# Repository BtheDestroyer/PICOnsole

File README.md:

# PICOnsole

Simple OS made from scratch for the Raspberry Pi Pico with the intention of being used to launch games.

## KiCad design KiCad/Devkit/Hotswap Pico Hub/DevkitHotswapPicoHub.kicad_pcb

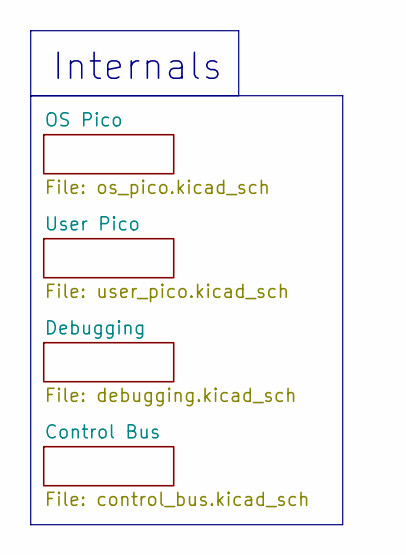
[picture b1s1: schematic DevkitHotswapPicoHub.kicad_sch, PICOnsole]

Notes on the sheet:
Internals

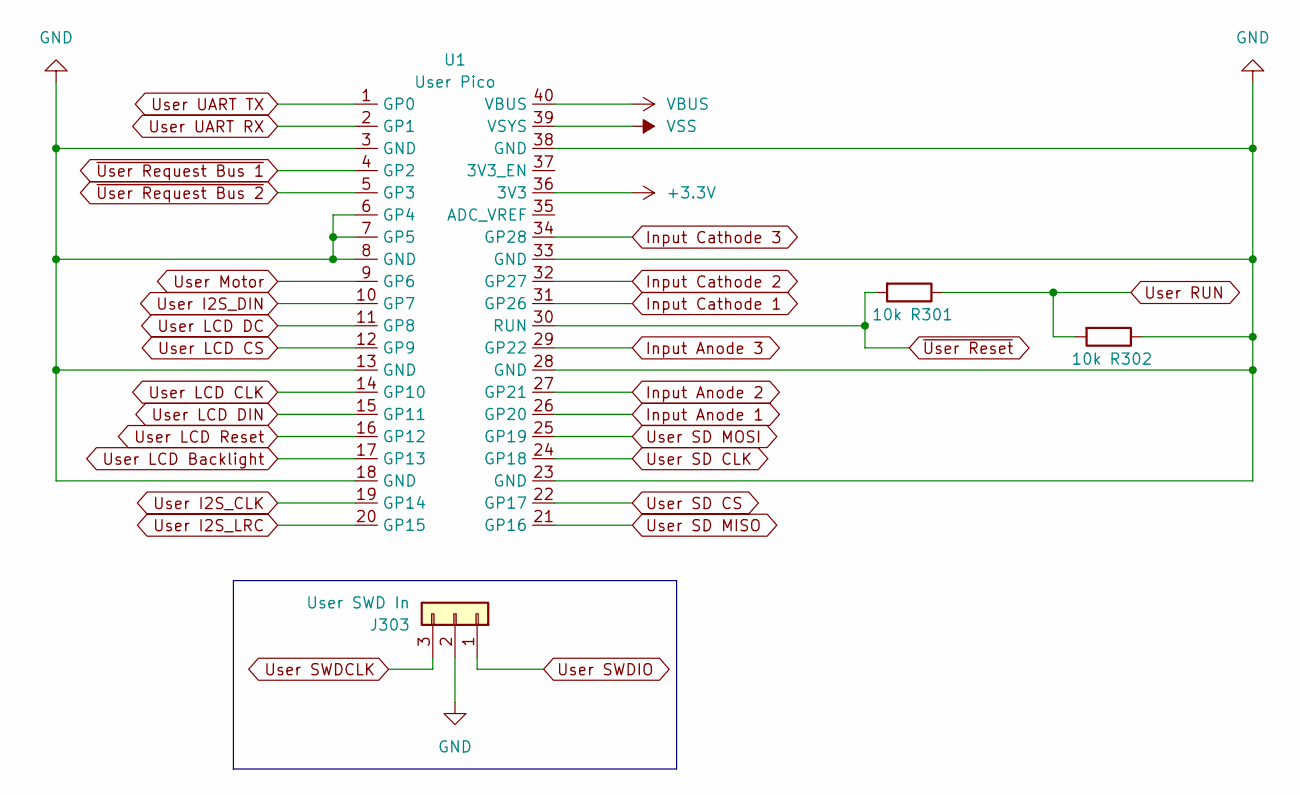
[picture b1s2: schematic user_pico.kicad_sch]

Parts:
J303: User SWD In; PinHeader_1x03_P2.54mm_Vertical
R301, R302: 10k; R_0805_2012Metric
U1: User Pico; Raspberry_Pi_Pico

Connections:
GND: J303.2, R302.1; also elsewhere on the board
User RUN: R301.1, R302.2; also elsewhere on the board
User SWDCLK: J303.3; also elsewhere on the board
User SWDIO: J303.1; also elsewhere on the board
~User Reset: R301.2; also elsewhere on the board

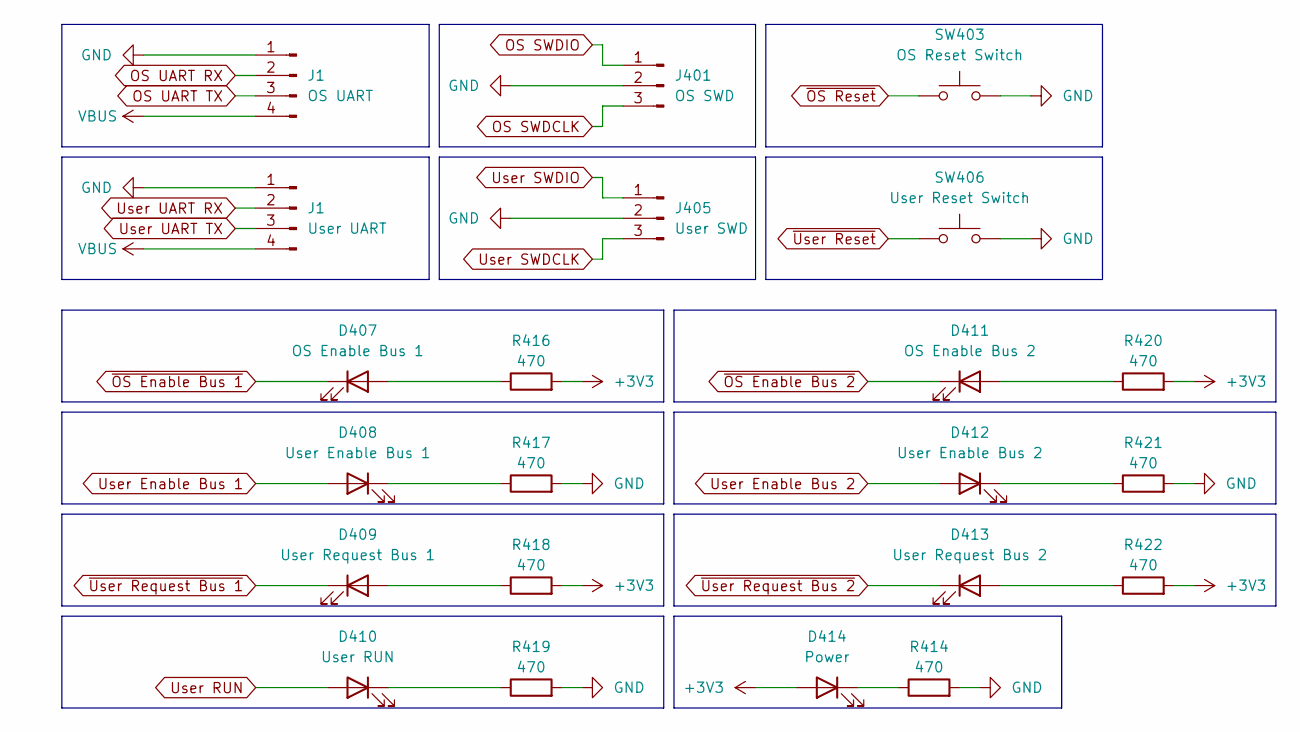
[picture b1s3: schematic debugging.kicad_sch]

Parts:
D407: OS Enable Bus 1; LED_D5.0mm
D408: User Enable Bus 1; LED_D5.0mm
D409: User Request Bus 1; LED_D5.0mm
D410: User RUN; LED_D5.0mm
D411: OS Enable Bus 2; LED_D5.0mm
D412: User Enable Bus 2; LED_D5.0mm
D413: User Request Bus 2; LED_D5.0mm
D414: Power; LED_D5.0mm
J1: OS UART; PinHeader_1x04_P2.54mm_Vertical
J401: OS SWD; PinSocket_1x03_P2.54mm_Vertical
J405: User SWD; PinSocket_1x03_P2.54mm_Vertical
R414, R416, R417, R418, R419, R420, R421, R422: 470; R_0805_2012Metric
SW403: OS Reset Switch; SW_PUSH-12mm
SW406: User Reset Switch; SW_PUSH-12mm

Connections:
GND: J401.2, J405.2, R414.2, R417.2, R419.2, R421.2, SW403.1, SW406.2; also elsewhere on the board
unnamed: D407.2 (A), R416.1
unnamed: D408.1 (K), R417.1
unnamed: D409.2 (A), R418.1
unnamed: D410.1 (K), R419.1
unnamed: D411.2 (A), R420.1
unnamed: D412.1 (K), R421.1
unnamed: D413.2 (A), R422.1
unnamed: D414.1 (K), R414.1
OS SWDCLK: J401.3; also elsewhere on the board
OS SWDIO: J401.1; also elsewhere on the board
User Enable Bus 1: D407.1 (K), D408.2 (A); also elsewhere on the board
User Enable Bus 2: D411.1 (K), D412.2 (A); also elsewhere on the board
User RUN: D410.2 (A); also elsewhere on the board
User SWDCLK: J405.3; also elsewhere on the board
User SWDIO: J405.1; also elsewhere on the board
~OS Reset: SW403.2; also elsewhere on the board
~User Request Bus 1: D409.1 (K); also elsewhere on the board
~User Request Bus 2: D413.1 (K); also elsewhere on the board
~User Reset: SW406.1; also elsewhere on the board

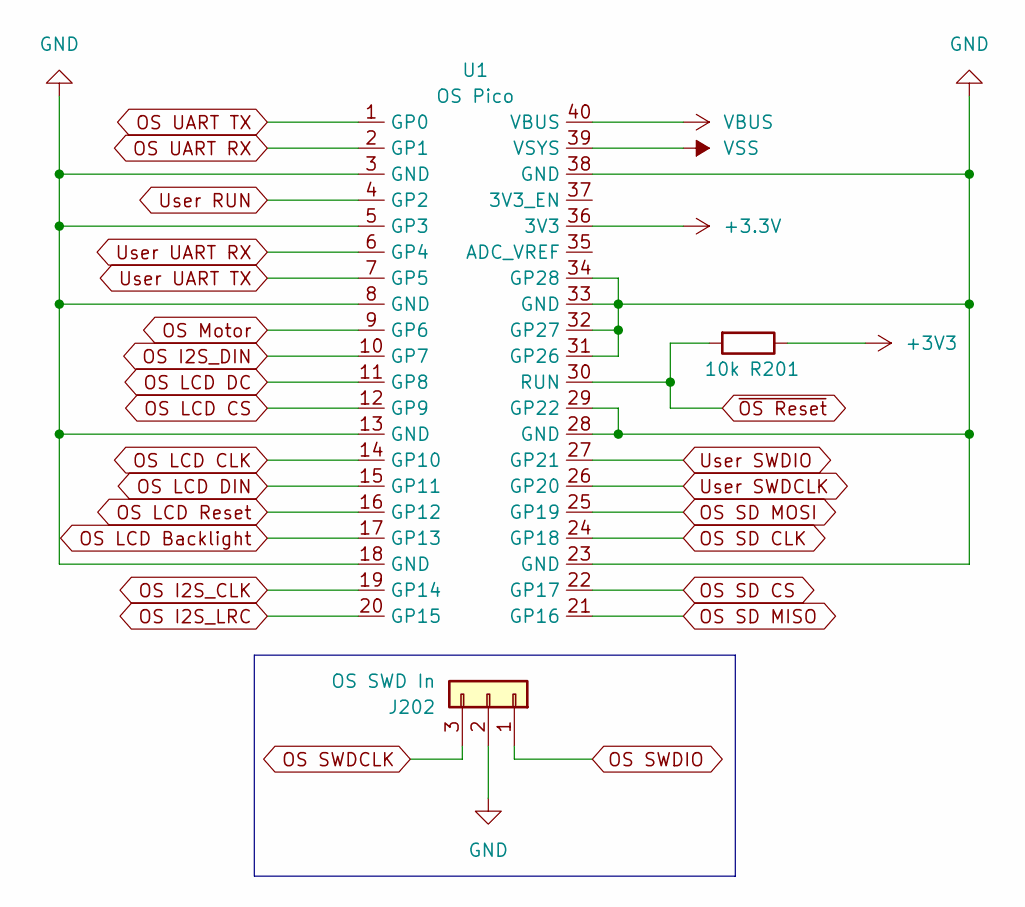
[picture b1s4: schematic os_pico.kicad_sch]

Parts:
J202: OS SWD In; PinHeader_1x03_P2.54mm_Vertical
R201: 10k; R_0805_2012Metric
U1: OS Pico; Raspberry_Pi_Pico

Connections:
GND: J202.2; also elsewhere on the board
OS SWDCLK: J202.3; also elsewhere on the board
OS SWDIO: J202.1; also elsewhere on the board
~OS Reset: R201.2; also elsewhere on the board

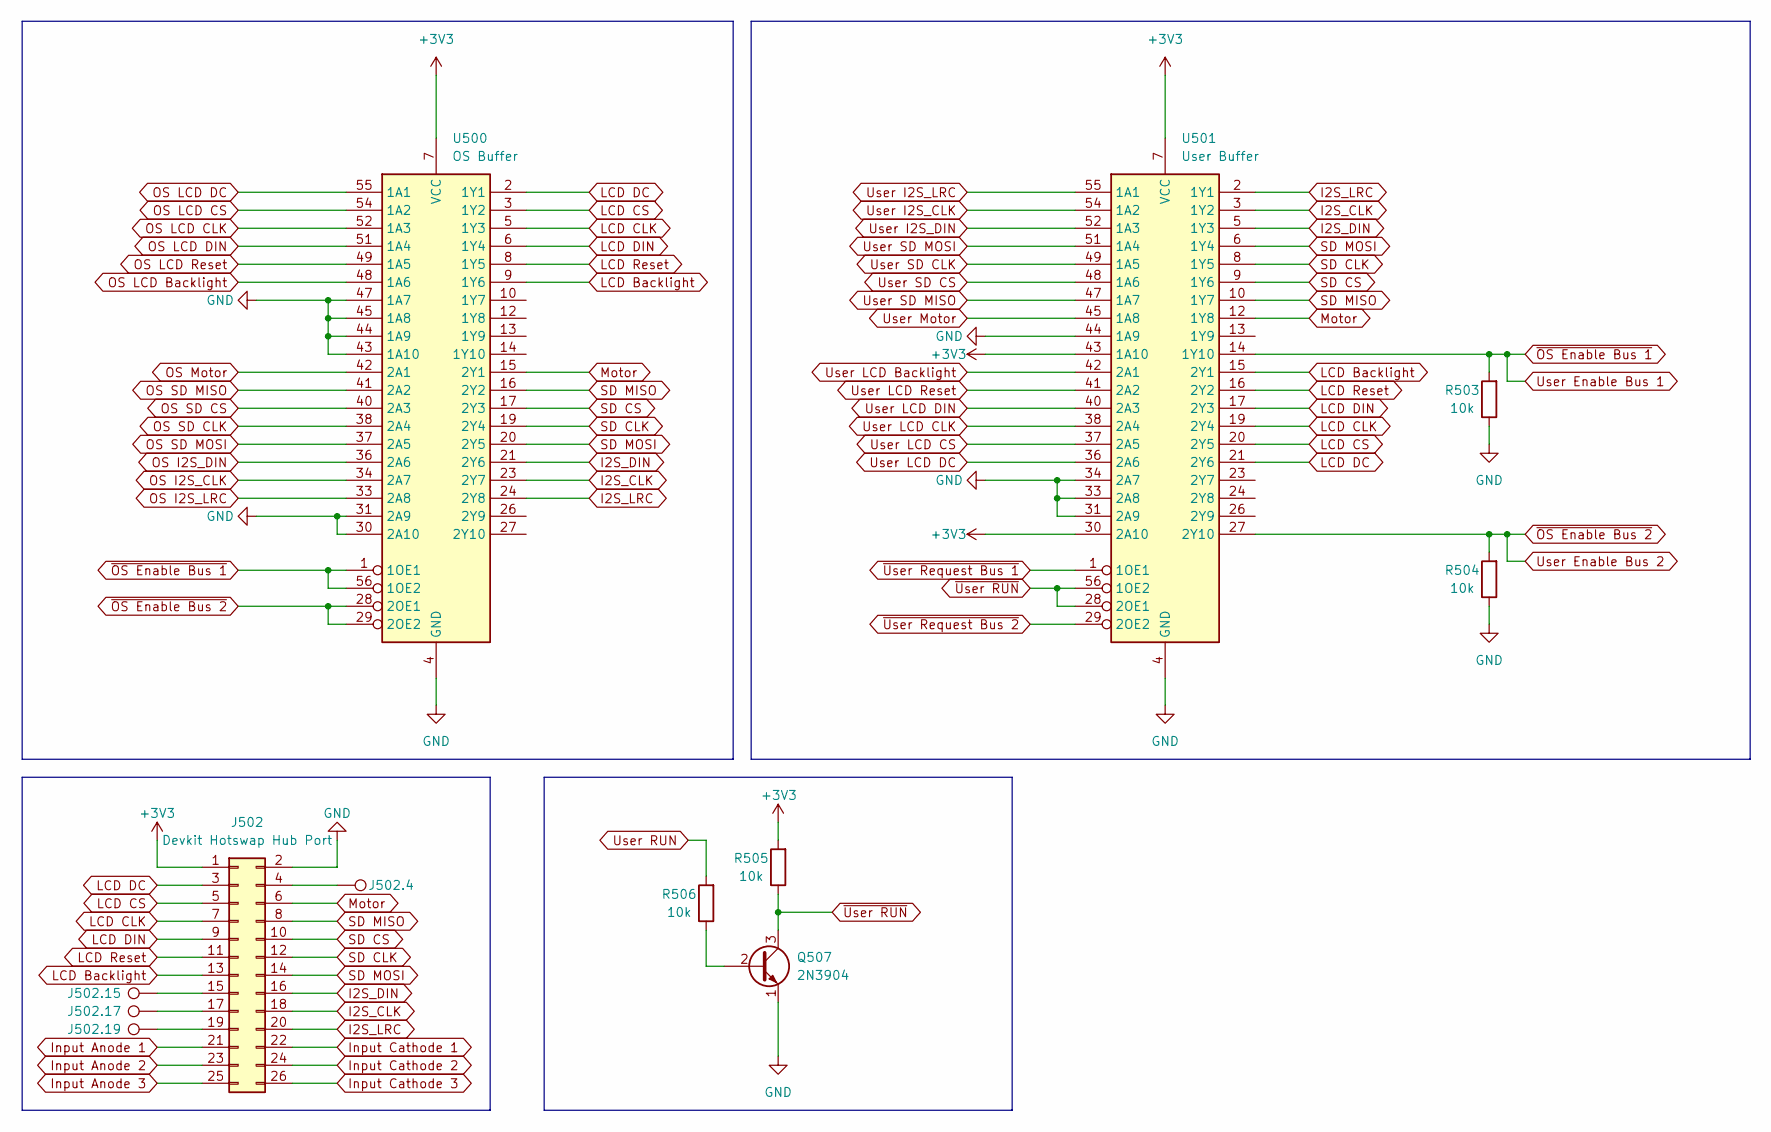
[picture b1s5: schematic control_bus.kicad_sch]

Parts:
J502: Devkit Hotswap Hub Port; PinHeader_2x13_P2.54mm_Vertical
J502.4, J502.15, J502.17, J502.19: TestPoint; TestPoint_Pad_1.5x1.5mm
Q507: 2N3904; TO-92_Inline
R503, R504, R505, R506: 10k; R_0805_2012Metric
U500: OS Buffer; TSSOP-56_6.1x14mm_P0.5mm
U501: User Buffer; TSSOP-56_6.1x14mm_P0.5mm

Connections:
GND: J502.2, Q507.1 (E), R503.1, R504.1, U500.4 (GND), U500.11 (GND), U500.18 (GND), U500.25 (GND), U500.30 (2A10), U500.31 (2A9), U500.32 (GND), U500.39 (GND), U500.43 (1A10), U500.44 (1A9), U500.45 (1A8), U500.46 (GND), U500.47 (1A7), U500.53 (GND), U501.4 (GND), U501.11 (GND), U501.18 (GND), U501.25 (GND), U501.31 (2A9), U501.32 (GND), U501.33 (2A8), U501.34 (2A7), U501.39 (GND), U501.44 (1A9), U501.46 (GND), U501.53 (GND); also elsewhere on the board
I2S_CLK: J502.18, U500.23 (2Y7), U501.3 (1Y2)
I2S_DIN: J502.16, U500.21 (2Y6), U501.5 (1Y3)
I2S_LRC: J502.20, U500.24 (2Y8), U501.2 (1Y1)
Input Anode 1: J502.21; also elsewhere on the board
Input Anode 2: J502.23; also elsewhere on the board
Input Anode 3: J502.25; also elsewhere on the board
Input Cathode 1: J502.22; also elsewhere on the board
Input Cathode 2: J502.24; also elsewhere on the board
Input Cathode 3: J502.26; also elsewhere on the board
LCD Backlight: J502.13, U500.9 (1Y6), U501.15 (2Y1)
LCD CLK: J502.7, U500.5 (1Y3), U501.19 (2Y4)
LCD CS: J502.5, U500.3 (1Y2), U501.20 (2Y5)
LCD DC: J502.3, U500.2 (1Y1), U501.21 (2Y6)
LCD DIN: J502.9, U500.6 (1Y4), U501.17 (2Y3)
LCD Reset: J502.11, U500.8 (1Y5), U501.16 (2Y2)
Motor: J502.6, U500.15 (2Y1), U501.12 (1Y8)
unnamed: J502.4, J502.4.1
unnamed: J502.15, J502.15.1
unnamed: J502.17, J502.17.1
unnamed: J502.19, J502.19.1
unnamed: Q507.2 (B), R506.1
OS I2S_CLK: U500.34 (2A7); also elsewhere on the board
OS I2S_DIN: U500.36 (2A6); also elsewhere on the board
OS I2S_LRC: U500.33 (2A8); also elsewhere on the board
OS LCD Backlight: U500.48 (1A6); also elsewhere on the board
OS LCD CLK: U500.52 (1A3); also elsewhere on the board
OS LCD CS: U500.54 (1A2); also elsewhere on the board
OS LCD DC: U500.55 (1A1); also elsewhere on the board
OS LCD DIN: U500.51 (1A4); also elsewhere on the board
OS LCD Reset: U500.49 (1A5); also elsewhere on the board
OS Motor: U500.42 (2A1); also elsewhere on the board
OS SD CLK: U500.38 (2A4); also elsewhere on the board
OS SD CS: U500.40 (2A3); also elsewhere on the board
OS SD MISO: U500.41 (2A2); also elsewhere on the board
OS SD MOSI: U500.37 (2A5); also elsewhere on the board
SD CLK: J502.12, U500.19 (2Y4), U501.8 (1Y5)
SD CS: J502.10, U500.17 (2Y3), U501.9 (1Y6)
SD MISO: J502.8, U500.16 (2Y2), U501.10 (1Y7)
SD MOSI: J502.14, U500.20 (2Y5), U501.6 (1Y4)
User Enable Bus 1: R503.2, U500.1 (1OE1), U500.56 (1OE2), U501.14 (1Y10); also elsewhere on the board
User Enable Bus 2: R504.2, U500.28 (2OE1), U500.29 (2OE2), U501.27 (2Y10); also elsewhere on the board
User I2S_CLK: U501.54 (1A2); also elsewhere on the board
User I2S_DIN: U501.52 (1A3); also elsewhere on the board
User I2S_LRC: U501.55 (1A1); also elsewhere on the board
User LCD Backlight: U501.42 (2A1); also elsewhere on the board
User LCD CLK: U501.38 (2A4); also elsewhere on the board
User LCD CS: U501.37 (2A5); also elsewhere on the board
User LCD DC: U501.36 (2A6); also elsewhere on the board
User LCD DIN: U501.40 (2A3); also elsewhere on the board
User LCD Reset: U501.41 (2A2); also elsewhere on the board
User Motor: U501.45 (1A8); also elsewhere on the board
User RUN: R506.2; also elsewhere on the board
User SD CLK: U501.49 (1A5); also elsewhere on the board
User SD CS: U501.48 (1A6); also elsewhere on the board
User SD MISO: U501.47 (1A7); also elsewhere on the board
User SD MOSI: U501.51 (1A4); also elsewhere on the board
~User RUN: Q507.3 (C), R505.1, U501.28 (2OE1), U501.56 (1OE2)
~User Request Bus 1: U501.1 (1OE1); also elsewhere on the board
~User Request Bus 2: U501.29 (2OE2); also elsewhere on the board

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
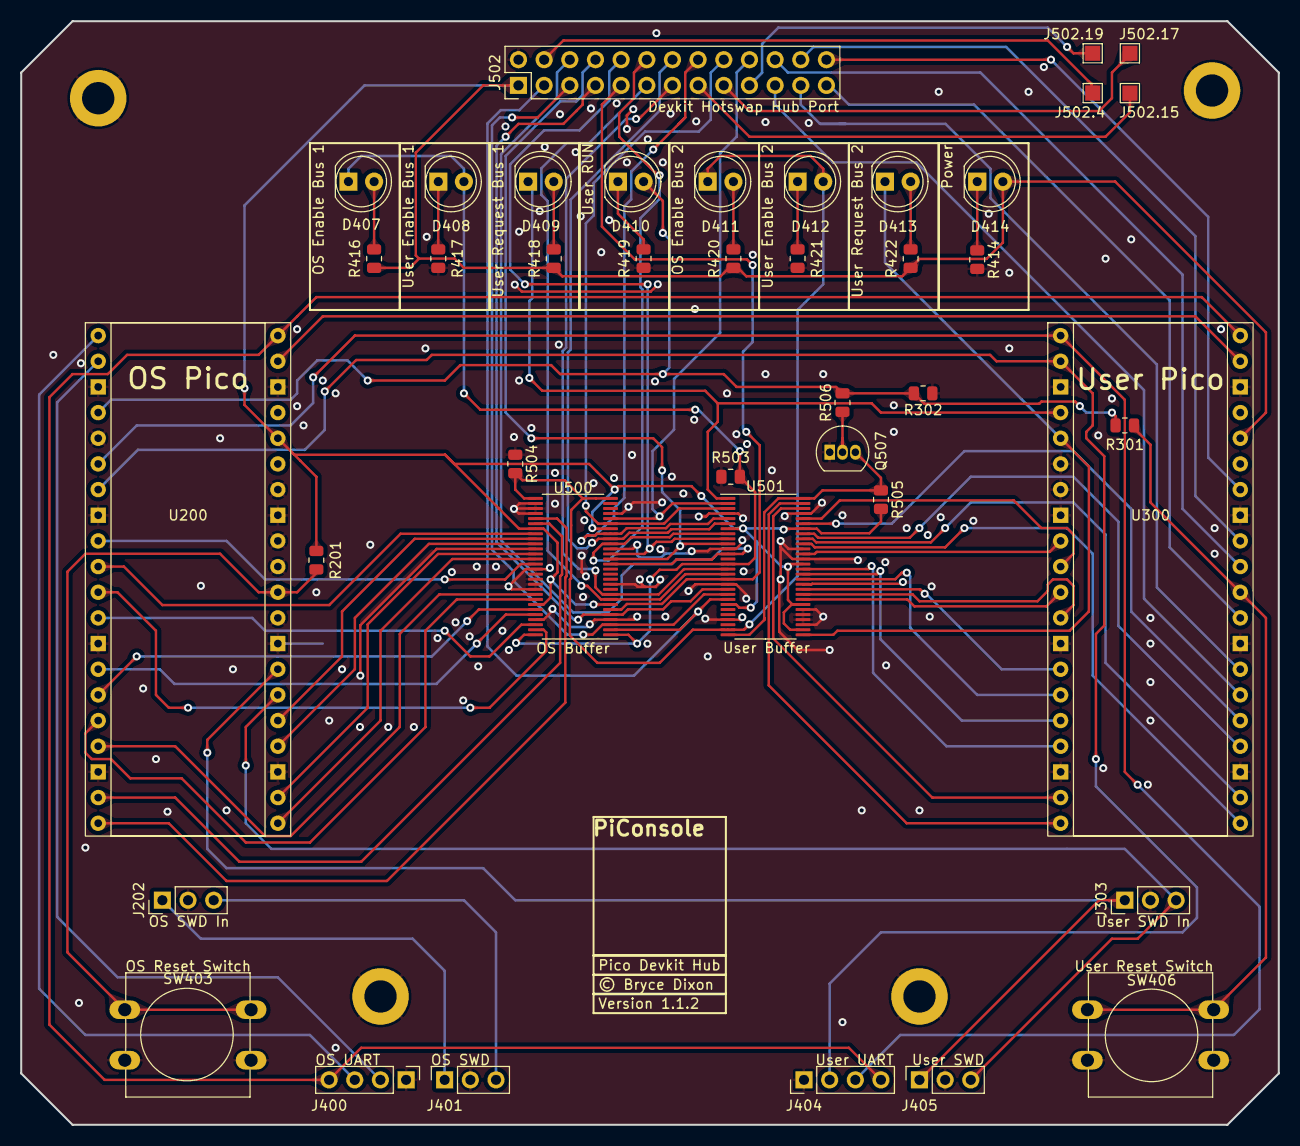
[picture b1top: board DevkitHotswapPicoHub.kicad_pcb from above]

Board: 2 copper layers, 124.5 x 109.2 mm, 41 parts (0 on the bottom side), 81 nets.

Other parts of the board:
J400: OS UART; PinHeader_1x04_P2.54mm_Vertical
J404: User UART; PinHeader_1x04_P2.54mm_Vertical
U200: OS Pico; Raspberry_Pi_Pico
U300: User Pico; Raspberry_Pi_Pico

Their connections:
GND: J400.1, J404.1, U200.3 (GND), U200.5 (GP3), U200.8 (GND), U200.13 (GND), U200.18 (GND), U200.23 (GND), U200.28 (GND), U200.29 (GP22), U200.31 (GP26), U200.32 (GP27), U200.33 (GND), U200.34 (GP28), U200.38 (GND), U300.3 (GND), U300.6 (GP4), U300.7 (GP5), U300.8 (GND), U300.13 (GND), U300.18 (GND), U300.23 (GND), U300.28 (GND), U300.33 (GND), U300.38 (GND); also elsewhere on the board
Input Anode 1: U300.26 (GP20); also elsewhere on the board
Input Anode 2: U300.27 (GP21); also elsewhere on the board
Input Anode 3: U300.29 (GP22); also elsewhere on the board
Input Cathode 1: U300.31 (GP26); also elsewhere on the board
Input Cathode 2: U300.32 (GP27); also elsewhere on the board
Input Cathode 3: U300.34 (GP28); also elsewhere on the board
OS I2S_CLK: U200.19 (GP14); also elsewhere on the board
OS I2S_DIN: U200.10 (GP7); also elsewhere on the board
OS I2S_LRC: U200.20 (GP15); also elsewhere on the board
OS LCD Backlight: U200.17 (GP13); also elsewhere on the board
OS LCD CLK: U200.14 (GP10); also elsewhere on the board
OS LCD CS: U200.12 (GP9); also elsewhere on the board
OS LCD DC: U200.11 (GP8); also elsewhere on the board
OS LCD DIN: U200.15 (GP11); also elsewhere on the board
OS LCD Reset: U200.16 (GP12); also elsewhere on the board
OS Motor: U200.9 (GP6); also elsewhere on the board
OS SD CLK: U200.24 (GP18); also elsewhere on the board
OS SD CS: U200.22 (GP17); also elsewhere on the board
OS SD MISO: U200.21 (GP16); also elsewhere on the board
OS SD MOSI: U200.25 (GP19); also elsewhere on the board
OS UART RX: J400.2, U200.2 (GP1)
OS UART TX: J400.3, U200.1 (GP0)
User I2S_CLK: U300.19 (GP14); also elsewhere on the board
User I2S_DIN: U300.10 (GP7); also elsewhere on the board
User I2S_LRC: U300.20 (GP15); also elsewhere on the board
User LCD Backlight: U300.17 (GP13); also elsewhere on the board
User LCD CLK: U300.14 (GP10); also elsewhere on the board
User LCD CS: U300.12 (GP9); also elsewhere on the board
User LCD DC: U300.11 (GP8); also elsewhere on the board
User LCD DIN: U300.15 (GP11); also elsewhere on the board
User LCD Reset: U300.16 (GP12); also elsewhere on the board
User Motor: U300.9 (GP6); also elsewhere on the board
User RUN: U200.4 (GP2); also elsewhere on the board
User SD CLK: U300.24 (GP18); also elsewhere on the board
User SD CS: U300.22 (GP17); also elsewhere on the board
User SD MISO: U300.21 (GP16); also elsewhere on the board
User SD MOSI: U300.25 (GP19); also elsewhere on the board
User SWDCLK: U200.26 (GP20); also elsewhere on the board
User SWDIO: U200.27 (GP21); also elsewhere on the board
User UART RX: J404.2, U200.6 (GP4), U300.2 (GP1)
User UART TX: J404.3, U200.7 (GP5), U300.1 (GP0)
VBUS: J400.4, J404.4, U200.40 (VBUS), U300.40 (VBUS)
VSS: U200.39 (VSYS), U300.39 (VSYS)
~OS Reset: U200.30 (RUN); also elsewhere on the board
~User Request Bus 1: U300.4 (GP2); also elsewhere on the board
~User Request Bus 2: U300.5 (GP3); also elsewhere on the board
~User Reset: U300.30 (RUN); also elsewhere on the board

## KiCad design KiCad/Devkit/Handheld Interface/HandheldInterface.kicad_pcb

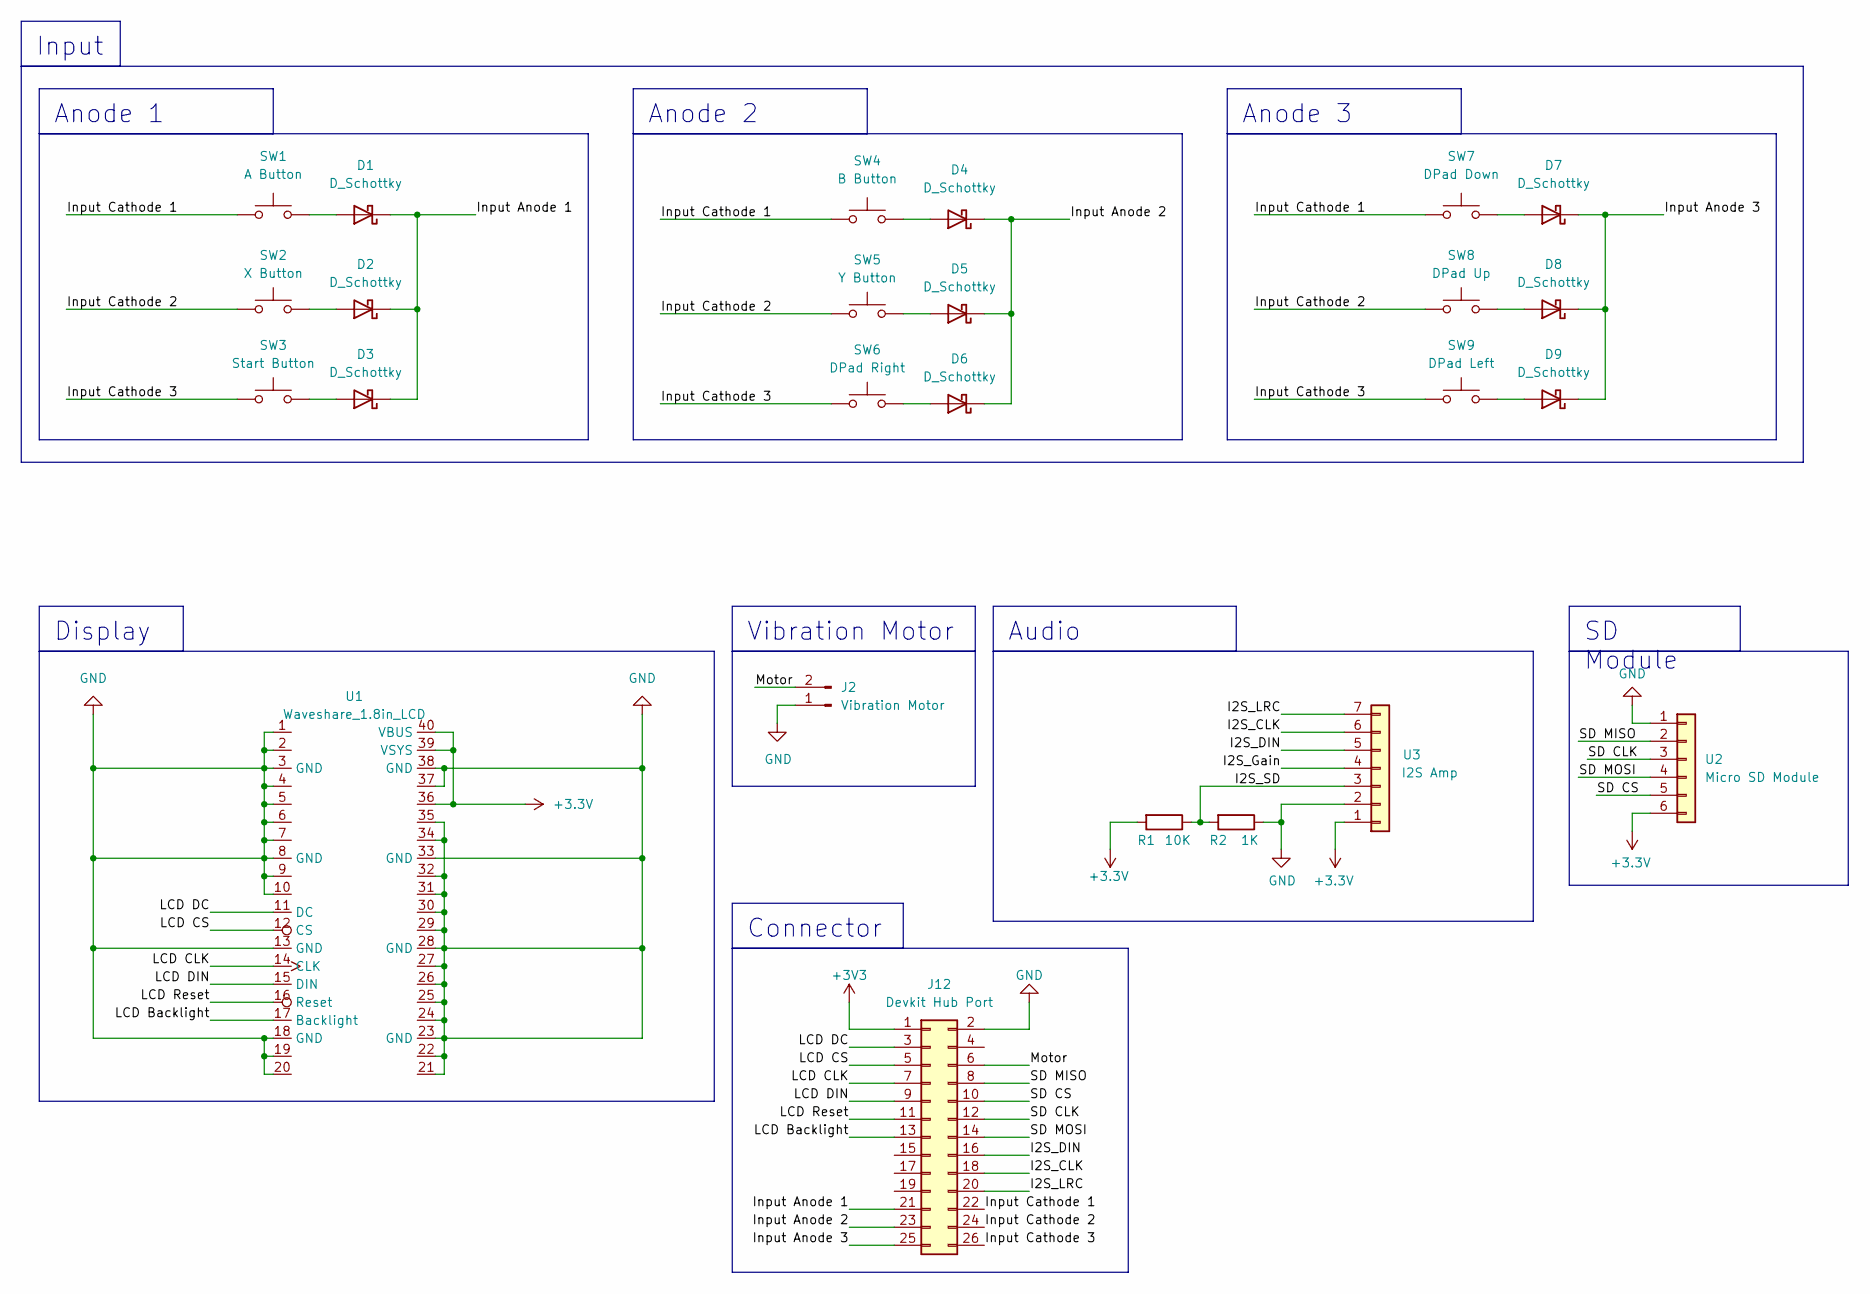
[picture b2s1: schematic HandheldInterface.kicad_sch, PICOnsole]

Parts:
D1, D2, D3, D4, D5, D6, D7, D8, D9: D_Schottky; D_A-405_P10.16mm_Horizontal
J2: Vibration Motor; PinHeader_1x02_P2.54mm_Vertical
J12: Devkit Hub Port; PinHeader_2x13_P2.54mm_Vertical
R1: 10K; R_0805_2012Metric_Pad1.20x1.40mm_HandSolder
R2: 1K; R_0805_2012Metric_Pad1.20x1.40mm_HandSolder
SW1: A Button; SW_PUSH-12mm
SW2: X Button; SW_PUSH-12mm
SW3: Start Button; SW_PUSH_6mm
SW4: B Button; SW_PUSH-12mm
SW5: Y Button; SW_PUSH-12mm
SW6: DPad Right; SW_PUSH-12mm
SW7: DPad Down; SW_PUSH-12mm
SW8: DPad Up; SW_PUSH-12mm
SW9: DPad Left; SW_PUSH-12mm
U1: Waveshare_1.8in_LCD
U2: Micro SD Module; PinHeader_1x06_P2.54mm_Vertical
U3: I2S Amp; PinHeader_1x07_P2.54mm_Vertical

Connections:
/I2S_CLK: U3.6; also elsewhere on the board
/I2S_DIN: U3.5; also elsewhere on the board
/I2S_Gain: U3.4
/I2S_LRC: U3.7; also elsewhere on the board
/I2S_SD: R1.1, R2.2, U3.3
/Input Anode 1: D1.1 (K), D2.1 (K), D3.1 (K); also elsewhere on the board
/Input Anode 2: D4.1 (K), D5.1 (K), D6.1 (K); also elsewhere on the board
/Input Anode 3: D7.1 (K), D8.1 (K), D9.1 (K); also elsewhere on the board
/Input Cathode 1: SW1.1, SW4.1, SW7.1; also elsewhere on the board
/Input Cathode 2: SW2.1, SW5.1, SW8.1; also elsewhere on the board
/Input Cathode 3: SW3.1, SW6.1, SW9.1; also elsewhere on the board
/LCD Backlight: U1.17 (Backlight); also elsewhere on the board
/LCD CLK: U1.14 (CLK); also elsewhere on the board
/LCD CS: U1.12 (CS); also elsewhere on the board
/LCD DC: U1.11 (DC); also elsewhere on the board
/LCD DIN: U1.15 (DIN); also elsewhere on the board
/LCD Reset: U1.16 (Reset); also elsewhere on the board
/Motor: J2.2; also elsewhere on the board
/SD CLK: U2.3; also elsewhere on the board
/SD CS: U2.5; also elsewhere on the board
/SD MISO: U2.2; also elsewhere on the board
/SD MOSI: U2.4; also elsewhere on the board
GND: J2.1, R2.1, U1.1, U1.2, U1.3 (GND), U1.4, U1.5, U1.6, U1.7, U1.8 (GND), U1.9, U1.10, U1.13 (GND), U1.18 (GND), U1.19, U1.20, U1.21, U1.22, U1.23 (GND), U1.24, U1.25, U1.26, U1.27, U1.28 (GND), U1.29, U1.30, U1.31, U1.32, U1.33 (GND), U1.34, U1.35, U1.37, U1.38 (GND), U2.1, U3.2; also elsewhere on the board
unnamed: D1.2 (A), SW1.2
unnamed: D2.2 (A), SW2.2
unnamed: D3.2 (A), SW3.2
unnamed: D4.2 (A), SW4.2
unnamed: D5.2 (A), SW5.2
unnamed: D6.2 (A), SW6.2
unnamed: D7.2 (A), SW7.2
unnamed: D8.2 (A), SW8.2
unnamed: D9.2 (A), SW9.2

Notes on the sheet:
Input
Connector
Anode 3
Anode 2
Anode 1
Display
Vibration Motor
SD Module
Audio

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
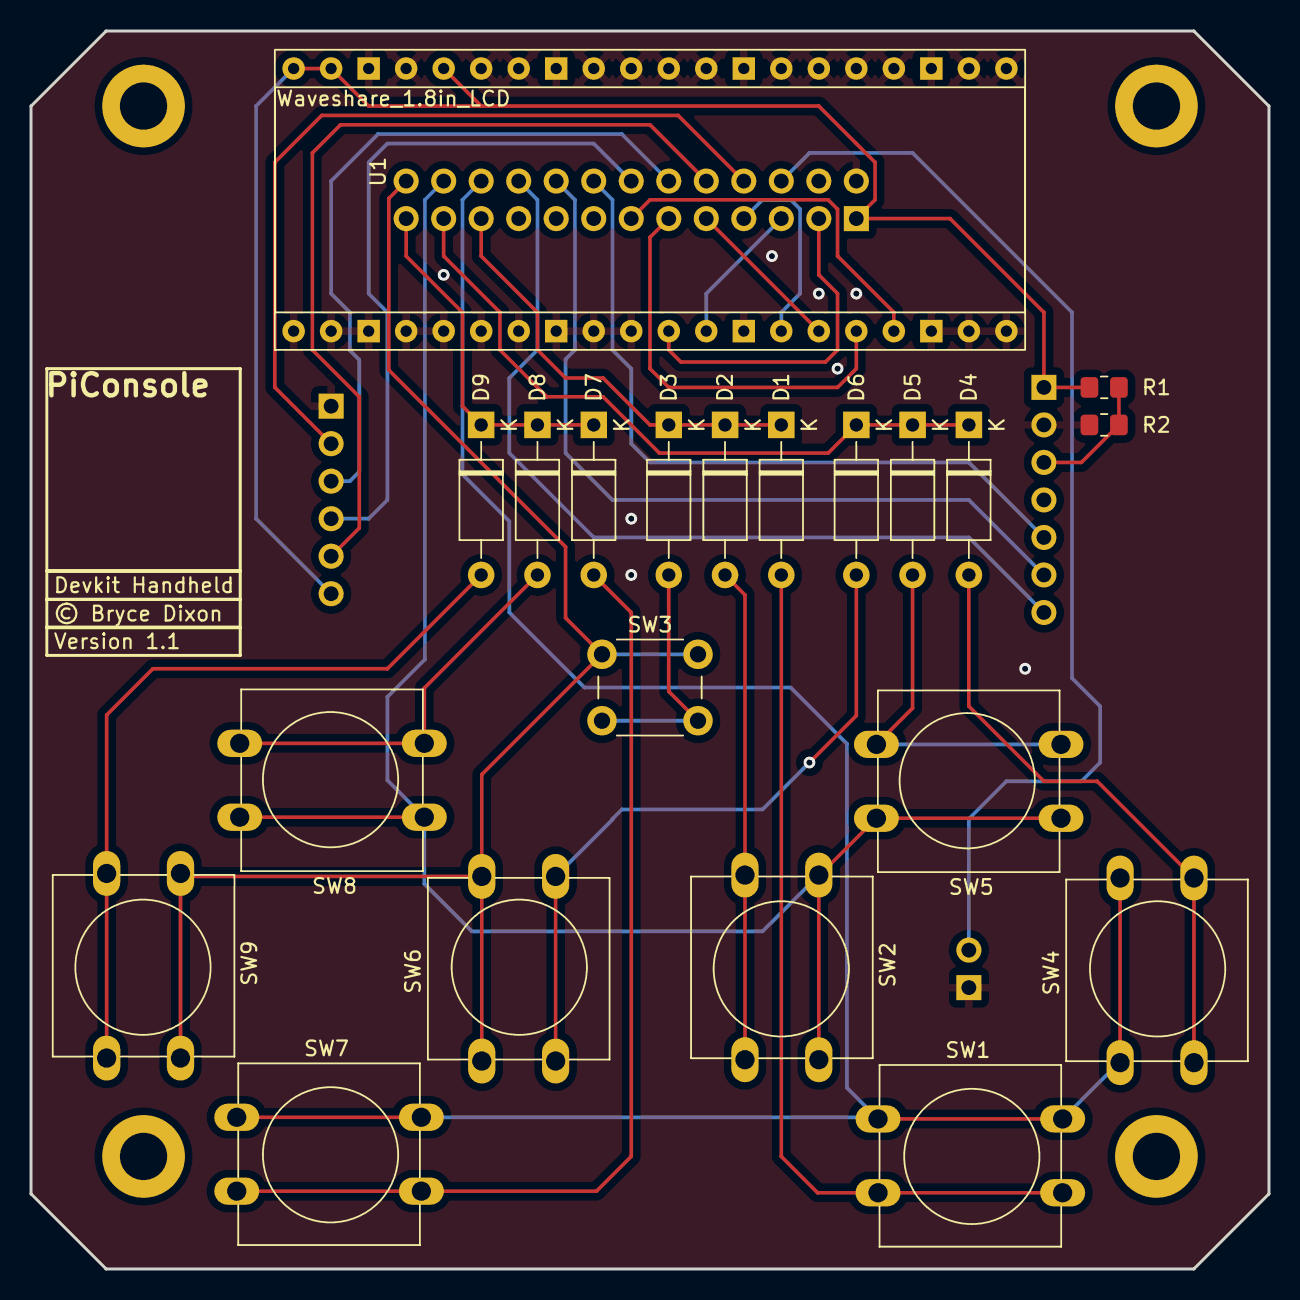
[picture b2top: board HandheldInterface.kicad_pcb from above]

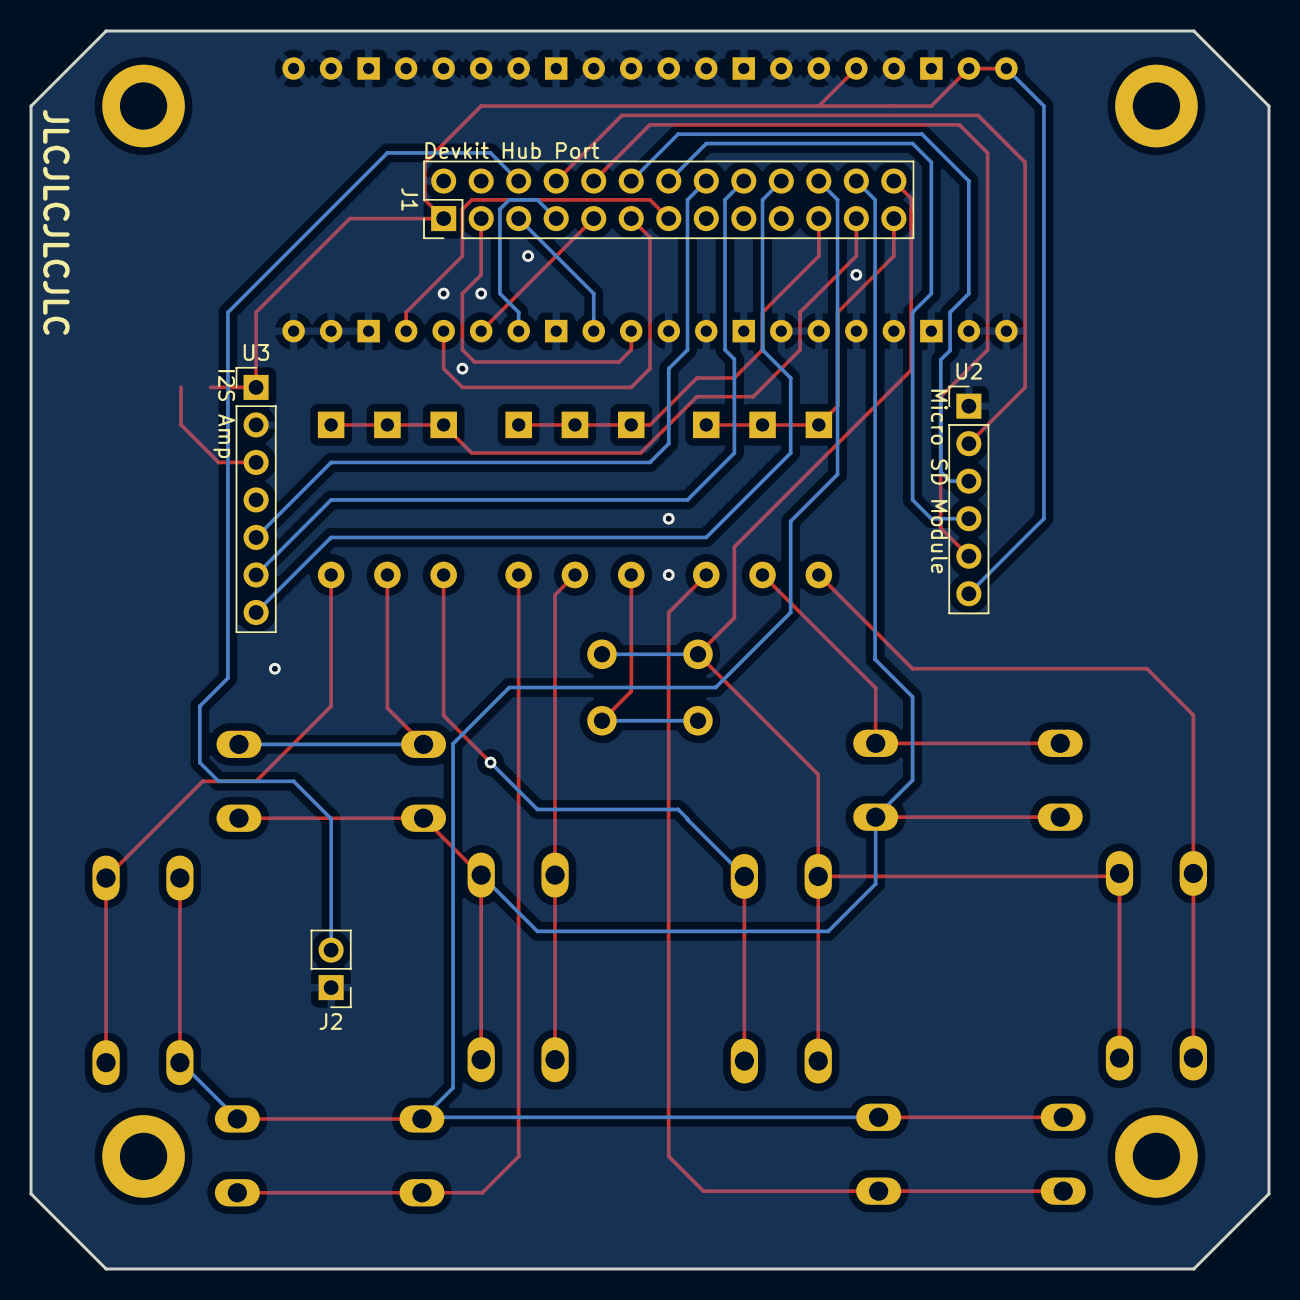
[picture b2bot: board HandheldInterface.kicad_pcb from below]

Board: 2 copper layers, 83.8 x 83.8 mm, 25 parts (4 on the bottom side), 32 nets.

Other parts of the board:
J1: Devkit Hub Port; PinHeader_2x13_P2.54mm_Vertical

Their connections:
/I2S_CLK: J1.18; also elsewhere on the board
/I2S_DIN: J1.16; also elsewhere on the board
/I2S_LRC: J1.20; also elsewhere on the board
/Input Anode 1: J1.21; also elsewhere on the board
/Input Anode 2: J1.23; also elsewhere on the board
/Input Anode 3: J1.25; also elsewhere on the board
/Input Cathode 1: J1.22; also elsewhere on the board
/Input Cathode 2: J1.24; also elsewhere on the board
/Input Cathode 3: J1.26; also elsewhere on the board
/LCD Backlight: J1.13; also elsewhere on the board
/LCD CLK: J1.7; also elsewhere on the board
/LCD CS: J1.5; also elsewhere on the board
/LCD DC: J1.3; also elsewhere on the board
/LCD DIN: J1.9; also elsewhere on the board
/LCD Reset: J1.11; also elsewhere on the board
/Motor: J1.6; also elsewhere on the board
/SD CLK: J1.12; also elsewhere on the board
/SD CS: J1.10; also elsewhere on the board
/SD MISO: J1.8; also elsewhere on the board
/SD MOSI: J1.14; also elsewhere on the board
GND: J1.2; also elsewhere on the board

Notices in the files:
KiCad/Devkit/Handheld Interface/HandheldInterface.kicad_pcb:
© Bryce Dixon
